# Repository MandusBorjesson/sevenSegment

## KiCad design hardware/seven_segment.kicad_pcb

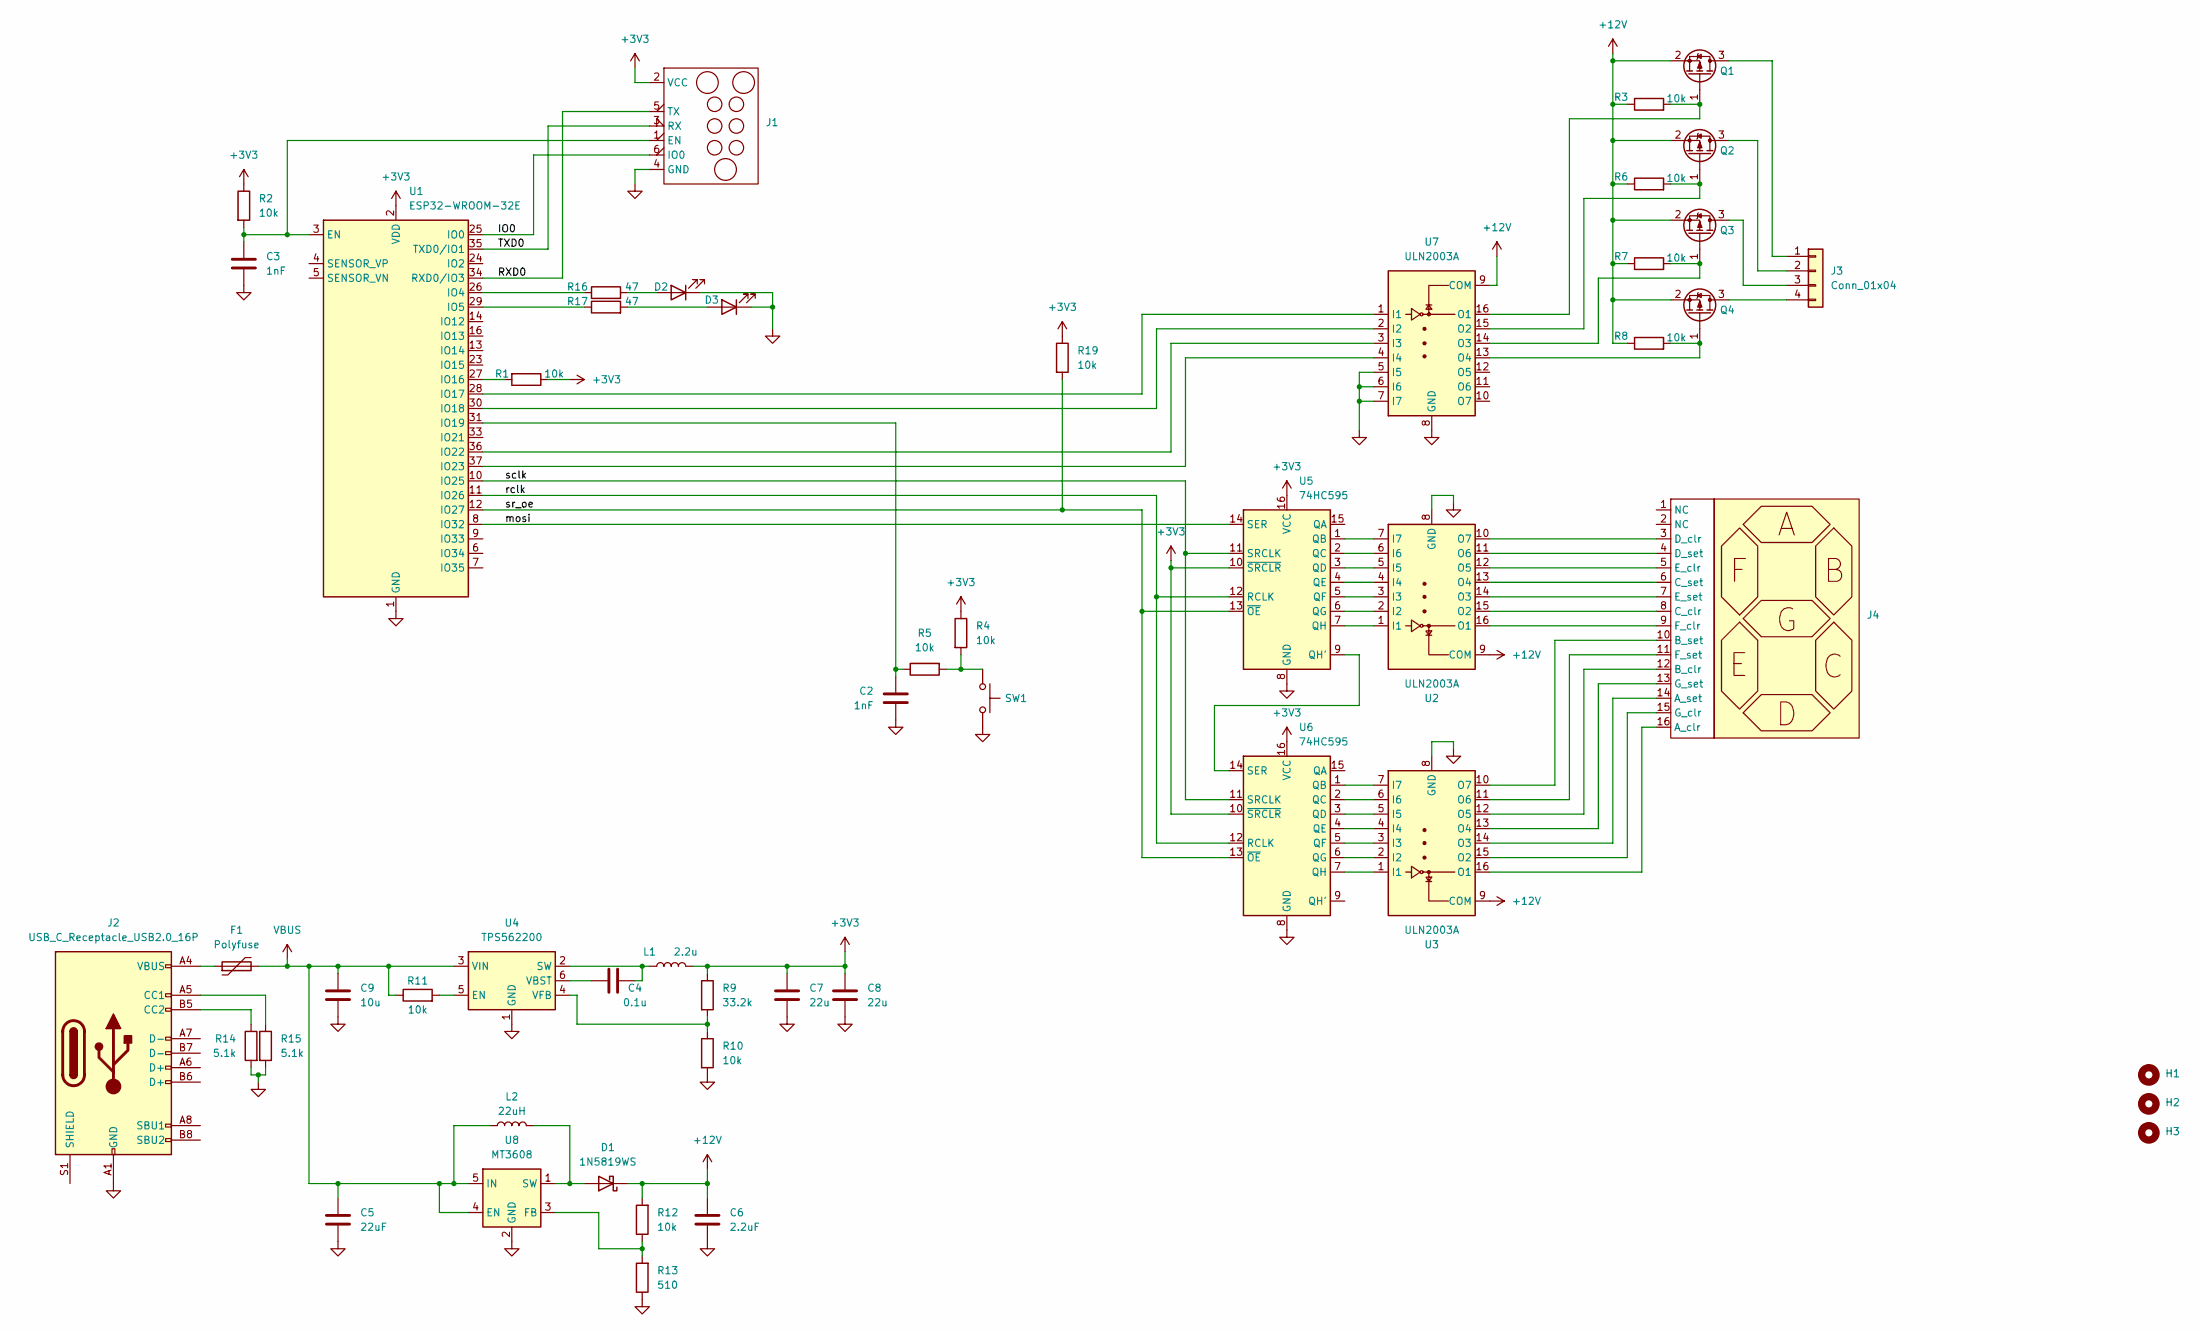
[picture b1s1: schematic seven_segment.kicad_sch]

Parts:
C2, C3: 1nF; R_0603_1608Metric
C4: 0.1u; R_0603_1608Metric
C5: 22uF; C_0805_2012Metric; LCSC Part C309062
C6: 2.2uF; C_1210_3225Metric; LCSC Part C153036
C7, C8: 22u; C_0805_2012Metric
C9: 10u; C_0805_2012Metric
D1: 1N5819WS; D_SOD-323; LCSC Part C191023
D2: LED; LED_0603_1608Metric; LCSC Part C2290
D3: LED; LED_0603_1608Metric; LCSC Part C84266
F1: Polyfuse; R_1210_3225Metric; LCSC Part C89653
H1, H2, H3: MountingHole; MountingHole_3mm
J1: Tag-Connect_TC2030-IDC-NL_2x03_P1.27mm_Vertical
J2: USB_C_Receptacle_USB2.0_16P; USB_C_Receptacle_GCT_USB4105-xx-A_16P_TopMnt_Horizontal
J3: Conn_01x04; JST_EH_B4B-EH-A_1x04_P2.50mm_Vertical
J4: PinHeader_2x08_P2.54mm_Vertical_SMD
L1: 2.2u; L_Vishay_IHLP-1212
L2: 22uH; L_Bourns_SRN6045TA; LCSC Part C780213
Q1, Q2, Q3, Q4: IRLML5203; SOT-23
R1, R2, R3, R4, R5, R6, R7, R8, R10, R11, R19: 10k; R_0603_1608Metric
R9: 33.2k; R_0603_1608Metric
R12: 10k; R_0603_1608Metric; LCSC Part C4184
R13: 510; R_0603_1608Metric; LCSC Part C23179
R14, R15: 5.1k; R_0603_1608Metric
R16, R17: 47; R_0603_1608Metric
SW1: SW_Push; SW_SPST_CK_RS282G05A3
U1: ESP32-WROOM-32E; ESP32-WROOM-32D
U2, U3, U7: ULN2003A; SOP-16_3.9x9.9mm_P1.27mm
U4: TPS562200; SOT-23-6; LCSC Part# C411814
U5, U6: 74HC595; SOP-16_3.9x9.9mm_P1.27mm
U8: MT3608; SOT-23-6; LCSC Part C84817

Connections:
+3V3: C7.1, C8.1, J1.2 (VCC), L1.2, R1.1, R2.1, R4.1, R9.1, R19.1, U1.2 (VDD), U5.10 (~SRCLR), U5.16 (VCC), U6.10 (~SRCLR), U6.16 (VCC)
+12V: C6.1, D1.1 (K), Q1.2 (S), Q2.2 (S), Q3.2 (S), Q4.2 (S), R3.1, R6.1, R7.1, R8.1, R12.2, U2.9 (COM), U3.9 (COM), U7.9 (COM)
/IO0: J1.6 (IO0), U1.25 (IO0)
/RXD0: J1.5 (TX), U1.34 (RXD0/IO3)
/TXD0: J1.3 (RX), U1.35 (TXD0/IO1)
/mosi: U1.8 (IO32), U5.14 (SER)
/rclk: U1.11 (IO26), U5.12 (RCLK), U6.12 (RCLK)
/sclk: U1.10 (IO25), U5.11 (SRCLK), U6.11 (SRCLK)
/sr_oe: R19.2, U1.12 (IO27), U5.13 (~OE), U6.13 (~OE)
GND: C2.2, C3.2, C5.2, C6.2, C7.2, C8.2, C9.2, D2.1 (K), D3.1 (K), J1.4 (GND), J2.A1 (GND), J2.A12 (GND), J2.B1 (GND), J2.B12 (GND), R10.2, R13.1, R14.2, R15.2, SW1.2, U1.1 (GND), U1.15 (GND), U1.38 (GND), U1.39 (GND), U2.8 (GND), U3.8 (GND), U4.1 (GND), U5.8 (GND), U6.8 (GND), U7.5 (I5), U7.6 (I6), U7.7 (I7), U7.8 (GND), U8.2 (GND)
unnamed: D1.2 (A), L2.2, U8.1 (SW)
unnamed: D2.2 (A), R16.2
unnamed: D3.2 (A), R17.2
unnamed: F1.1, J2.A4 (VBUS), J2.A9 (VBUS), J2.B4 (VBUS), J2.B9 (VBUS)
unnamed: C3.1, J1.1 (EN), R2.2, U1.3 (EN)
unnamed: J2.A5 (CC1), R15.1
unnamed: J2.B5 (CC2), R14.1
unnamed: J3.1, Q1.3 (D)
unnamed: J3.2, Q2.3 (D)
unnamed: J3.3, Q3.3 (D)
unnamed: J3.4, Q4.3 (D)
unnamed: J4.16 (A_clr), U3.16 (O1)
unnamed: J4.14 (A_set), U3.14 (O3)
unnamed: J4.12 (B_clr), U3.12 (O5)
unnamed: J4.10 (B_set), U3.10 (O7)
unnamed: J4.8 (C_clr), U2.15 (O2)
unnamed: J4.6 (C_set), U2.13 (O4)
unnamed: J4.3 (D_clr), U2.10 (O7)
unnamed: J4.4 (D_set), U2.11 (O6)
unnamed: J4.5 (E_clr), U2.12 (O5)
unnamed: J4.7 (E_set), U2.14 (O3)
unnamed: J4.9 (F_clr), U2.16 (O1)
unnamed: J4.11 (F_set), U3.11 (O6)
unnamed: J4.15 (G_clr), U3.15 (O2)
unnamed: J4.13 (G_set), U3.13 (O4)
unnamed: Q1.1 (G), R3.2, U7.16 (O1)
unnamed: Q2.1 (G), R6.2, U7.15 (O2)
unnamed: Q3.1 (G), R7.2, U7.14 (O3)
unnamed: Q4.1 (G), R8.2, U7.13 (O4)
unnamed: R4.2, R5.2, SW1.1
unnamed: R16.1, U1.26 (IO4)
unnamed: R17.1, U1.29 (IO5)
unnamed: R1.2, U1.27 (IO16)
unnamed: U1.28 (IO17), U7.1 (I1)
unnamed: U1.30 (IO18), U7.2 (I2)
unnamed: C2.1, R5.1, U1.31 (IO19)
unnamed: U1.36 (IO22), U7.3 (I3)
unnamed: U1.37 (IO23), U7.4 (I4)
unnamed: U2.1 (I1), U5.7 (QH)
unnamed: U2.2 (I2), U5.6 (QG)
unnamed: U2.3 (I3), U5.5 (QF)
unnamed: U2.4 (I4), U5.4 (QE)
unnamed: U2.5 (I5), U5.3 (QD)
unnamed: U2.6 (I6), U5.2 (QC)
unnamed: U2.7 (I7), U5.1 (QB)
unnamed: U3.1 (I1), U6.7 (QH)
unnamed: U3.2 (I2), U6.6 (QG)
unnamed: U3.3 (I3), U6.5 (QF)
unnamed: U3.4 (I4), U6.4 (QE)
unnamed: U3.5 (I5), U6.3 (QD)
unnamed: U3.6 (I6), U6.2 (QC)
unnamed: U3.7 (I7), U6.1 (QB)
unnamed: R11.2, U4.5 (EN)
unnamed: C4.2, L1.1, U4.2 (SW)
unnamed: C4.1, U4.6 (VBST)
unnamed: R9.2, R10.1, U4.4 (VFB)
unnamed: U5.9 (QH'), U6.14 (SER)
unnamed: R12.1, R13.2, U8.3 (FB)
VBUS: C5.1, C9.1, F1.2, L2.1, R11.1, U4.3 (VIN), U8.4 (EN), U8.5 (IN)

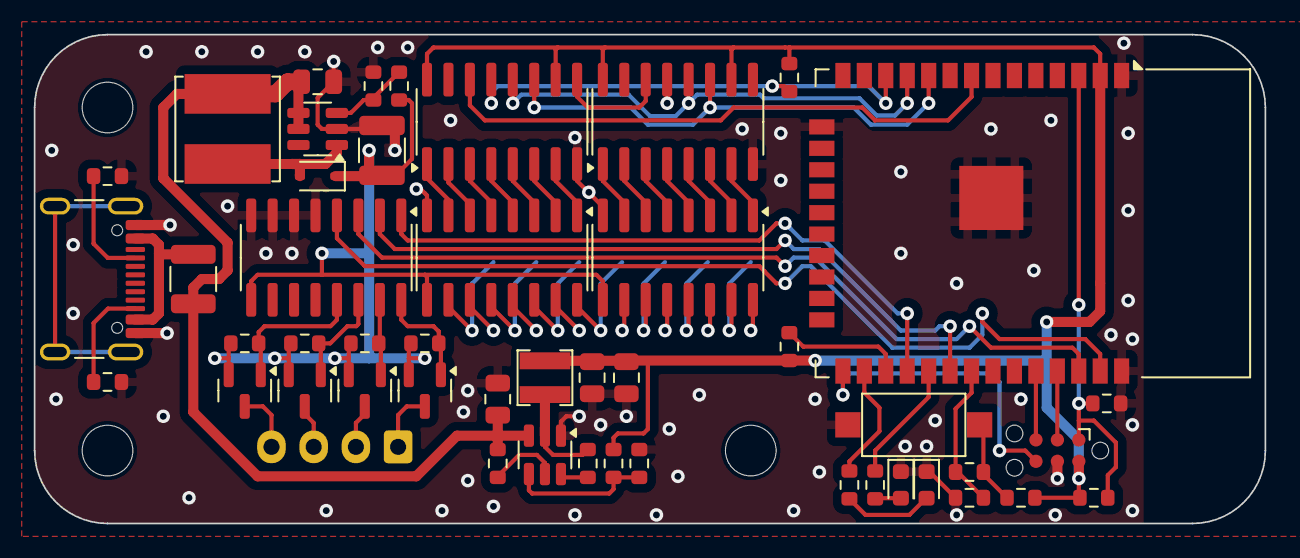
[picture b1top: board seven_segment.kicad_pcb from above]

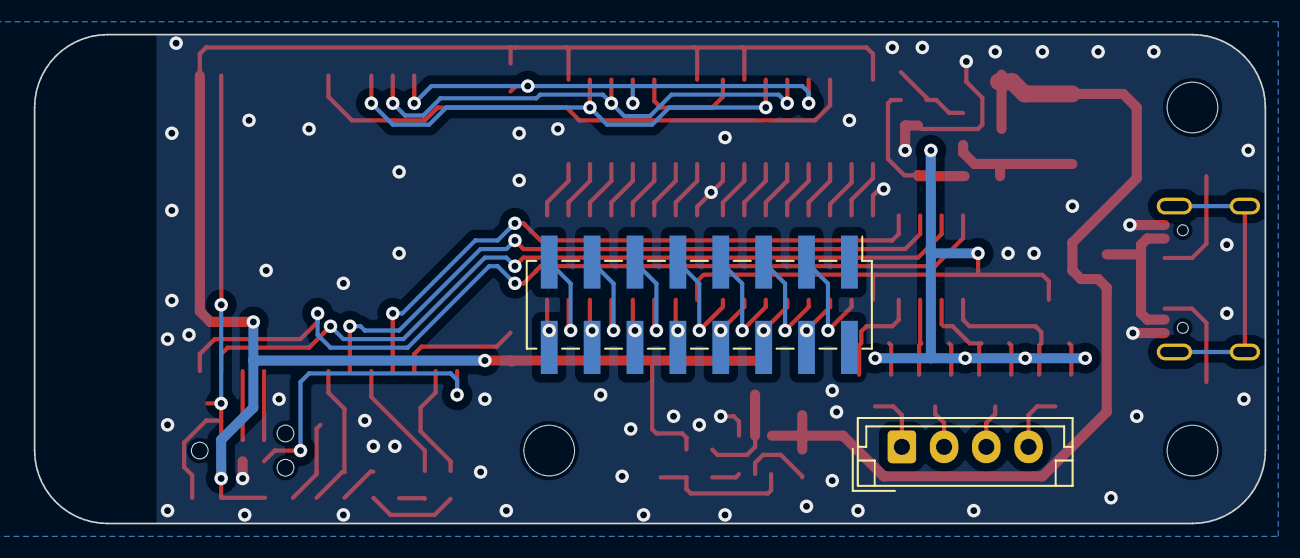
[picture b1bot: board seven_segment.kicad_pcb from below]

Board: 2 copper layers, 72.9 x 29.0 mm, 52 parts (2 on the bottom side), 69 nets.

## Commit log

2024-09-12 software: Initial commit
2024-09-12 software: Introduce some error types and return values
    The error types don't add much value at the moment since we have no way
    of handling the errors. The Ok values can be used to indicate wether a
    display update is required and speed up refreshes a bit.
2024-09-12 software: Make display count to infinity
2024-09-12 software: Remove Gpio template argument
    This was introduced in order to get things up and running before I knew
    better. I have since become (slightly) better at rust, allowing me to
    remove this maintenance nightmare.
2024-09-12 hardware: Start work on version 2
2024-09-12 software: Flashing works for STM32F103C8
2024-09-12 software: Blinky for stm32f1cc
2024-09-12 software: It works again
2024-09-12 software: Don't show leading zeros
2024-09-12 software: Add digit selector
    Currently, this conflicts a bit with the caching in the `Segment` struct
    since it has no concept of a segment being present in multiple digits.
2024-09-12 hardware: Initial version
2024-09-12 hardware: Version 2
2024-09-12 software: Not currently working
2024-09-12 software: Move digit state cache to DigitController
    The application can handle any number of digits, and keeping that
    caching in the `Segment` struct makes little sense. Move if to the
    DigitController instead since it has a bit more context.
2024-09-12 hardware: Add .gitignore
2024-09-12 software: Counting up
2024-09-12 software: Start adding support for hardware revision 2
2024-09-12 software: doesnt work
2024-09-12 software: Revert "doesnt work"
    This reverts commit 89bd6fb2918e601c94c91c7ec90c00280a4ce5ac.
2024-09-12 software: Flipping one segment
2025-01-08 hardware: revision 3
2025-01-25 software: start setting up zephyr
2025-01-25 software: it works yoooo
2025-01-25 fixup! software: start setting up zephyr
2025-01-25 software: getting there... malloc errors...
2025-01-26 software: It builds and works, wohoo!
2025-01-26 hardware: migrate to kicad 8
2025-01-26 software: Blinky on a relay
2025-10-19 hardware: Add net labels to SPI channel
2025-10-19 software: Start meddling with SPI
2025-10-23 software: Start adding digit support
2025-10-23 software: Change tabs to spaces
2025-10-28 hardware: Add net labels to segment control pins
2025-10-30 software: digit support mostly complete
2025-11-02 software: digit control works
2025-11-04 hardware: revision 4
    Changelog:
    Load switching:
    - Move back to transistors rather than relays since they are
    more reliable, faster and quiter.
    Mechanics:
    - Ditch the hammond enclosure for a 3d-printed chassi.
2025-11-04 hardware: update gitignore
